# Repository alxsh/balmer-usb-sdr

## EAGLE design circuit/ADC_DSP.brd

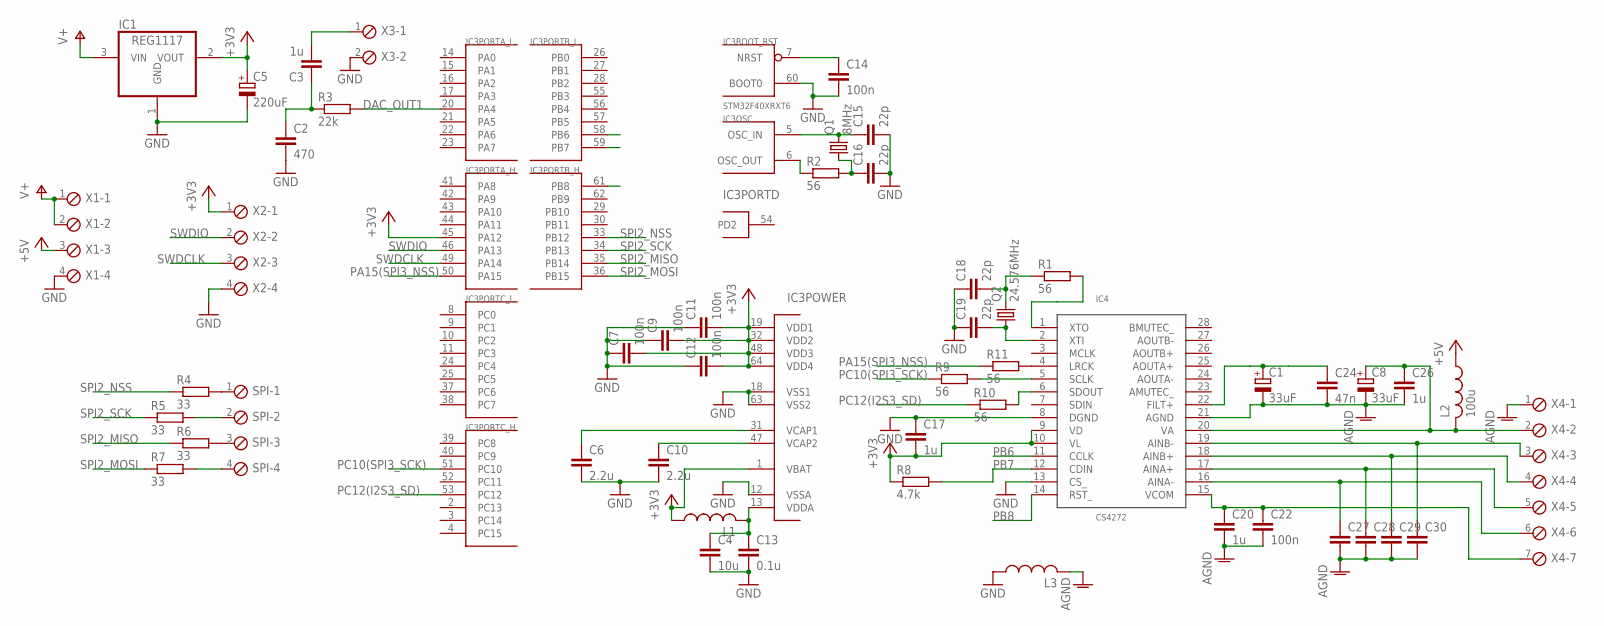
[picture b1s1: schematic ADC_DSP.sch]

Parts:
C1, C8: 33uF; 153CLV-0605
C2: 470; C0603
C3, C17, C20, C26: 1u; C0603
C4: 10u; C0805
C5: 220uF; 153CLV-0605
C6, C10: 2.2u; C0603
C7, C9, C11, C12, C14, C22: 100n; C0603
C13: 0.1u; C0603
C15, C16, C18, C19: 22p; C0603
C24: 47n; C0805
C27, C28, C29, C30: C-EUC0805; C0805
IC1: REG1117; SOT223
IC3: STM32F40XRXT6; TQFP64
IC4: CS4272; TSSOP28
L1, L3: L-USL2012C; L2012C
L2: 100u; 0207/12
Q1: 8MHz; HC49/S
Q2: 24.576MHz; HC49/S
R1, R2, R9, R10, R11: 56; R0603
R3: 22k; R0603
R4, R5, R6, R7: 33; R0603
R8: 4.7k; R0603
SPI: MPT4; 4POL254
X1, X2: MPT4; 4POL254
X3: MPT2; 2POL254
X4: MPT7; 7POL254

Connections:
+3V3: C5.+, C7.2, C9.2, C11.2, C12.2, C17.2, IC1.2 (VOUT), IC3.1 (VBAT), IC3.19 (VDD1), IC3.32 (VDD2), IC3.45 (PA12), IC3.48 (VDD3), IC3.64 (VDD4), IC4.9 (VD), IC4.10 (VL), L1.1, R8.1, X2.1
+5V: L2.1, X1.3
AGND: C1.-, C8.-, C20.2, C22.2, C24.2, C26.2, C27.2, C28.2, C29.2, C30.2, IC4.21 (AGND), L3.2, X4.1
AINA+: C28.1, IC4.17 (AINA+), X4.5
AINB+: C29.1, IC4.18 (AINB+), X4.4
AVCC: C8.+, C26.1, IC4.20 (VA), L2.2, X4.2
DAC_OUT1: IC3.20 (PA4), R3.2
GND: C2.2, C4.2, C5.-, C6.2, C7.1, C9.1, C10.2, C11.1, C12.1, C13.2, C14.2, C15.2, C16.2, C17.1, C18.1, C19.1, IC1.1 (GND), IC3.12 (VSSA), IC3.18 (VSS1), IC3.60 (BOOT0), IC3.63 (VSS2), IC4.8 (DGND), IC4.13 (CS_), L3.1, X1.4, X2.4, X3.2
unnamed: C10.1, IC3.47 (VCAP2)
unnamed: C6.1, IC3.31 (VCAP1)
unnamed: C4.1, C13.1, IC3.13 (VDDA), L1.2
unnamed: C14.1, IC3.7 (NRST)
unnamed: C15.1, IC3.5 (OSC_IN), Q1.2
unnamed: C16.1, Q1.1, R2.2
unnamed: C19.2, IC4.2 (XTI), Q2.1
unnamed: C18.2, Q2.2, R1.1
unnamed: IC4.4 (LRCK), R11.2
unnamed: IC4.5 (SCLK), R9.2
unnamed: IC4.6 (SDOUT), R10.2
unnamed: C1.+, C24.1, IC4.22 (FILT+)
unnamed: C30.1, IC4.19 (AINB-), X4.3
unnamed: C3.2, X3.1
unnamed: IC4.1 (XTO), R1.2
unnamed: C27.1, IC4.16 (AINA-), X4.6
unnamed: IC3.6 (OSC_OUT), R2.1
unnamed: R4.2, SPI.1
unnamed: R5.2, SPI.2
unnamed: R6.2, SPI.3
unnamed: C2.1, C3.1, R3.1
unnamed: R7.2, SPI.4
PA15(SPI3_NSS): IC3.50 (PA15), R11.1
PB6: IC3.58 (PB6), IC4.11 (CCLK)
PB7: IC3.59 (PB7), IC4.12 (CDIN), R8.2
PB8: IC3.61 (PB8), IC4.14 (RST_)
PC10(SPI3_SCK): IC3.51 (PC10), R9.1
PC12(I2S3_SD): IC3.53 (PC12), R10.1
SPI2_MISO: IC3.35 (PB14), R6.1
SPI2_MOSI: IC3.36 (PB15), R7.1
SPI2_NSS: IC3.33 (PB12), R4.1
SPI2_SCK: IC3.34 (PB13), R5.1
SWDCLK: IC3.49 (PA14), X2.3
SWDIO: IC3.46 (PA13), X2.2
V+: IC1.3 (VIN), X1.1, X1.2
VCOM: C20.1, C22.1, IC4.15 (VCOM), X4.7

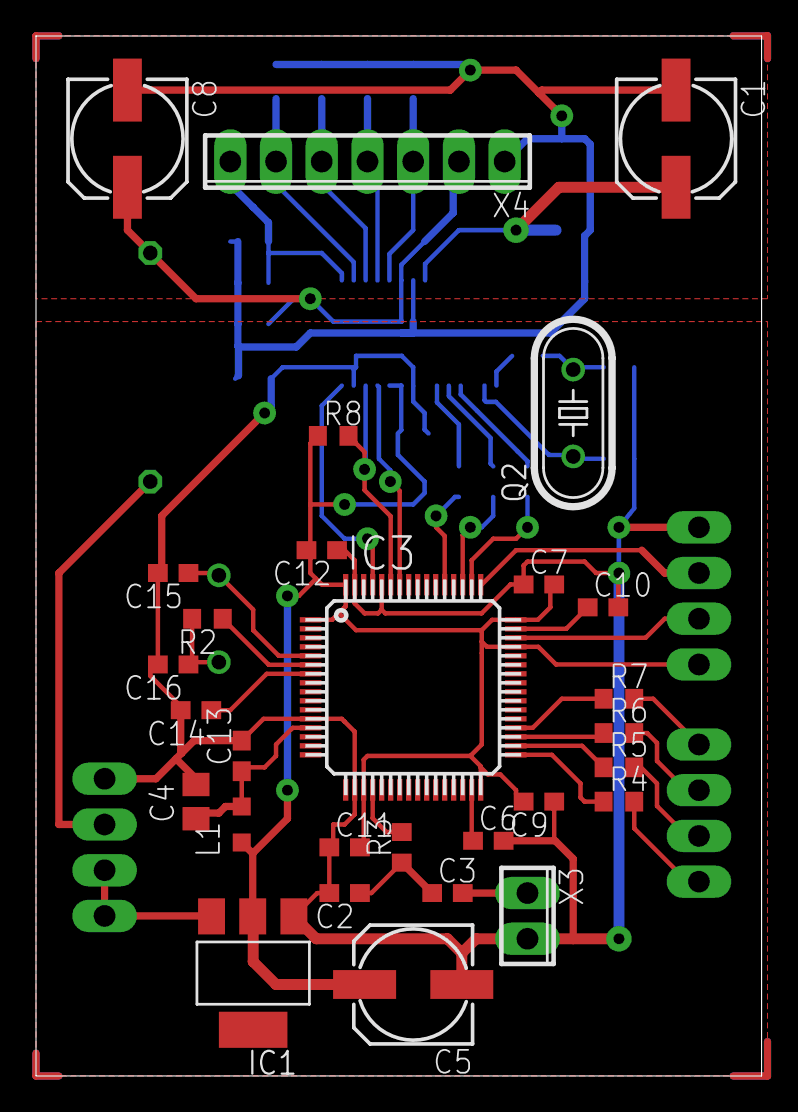
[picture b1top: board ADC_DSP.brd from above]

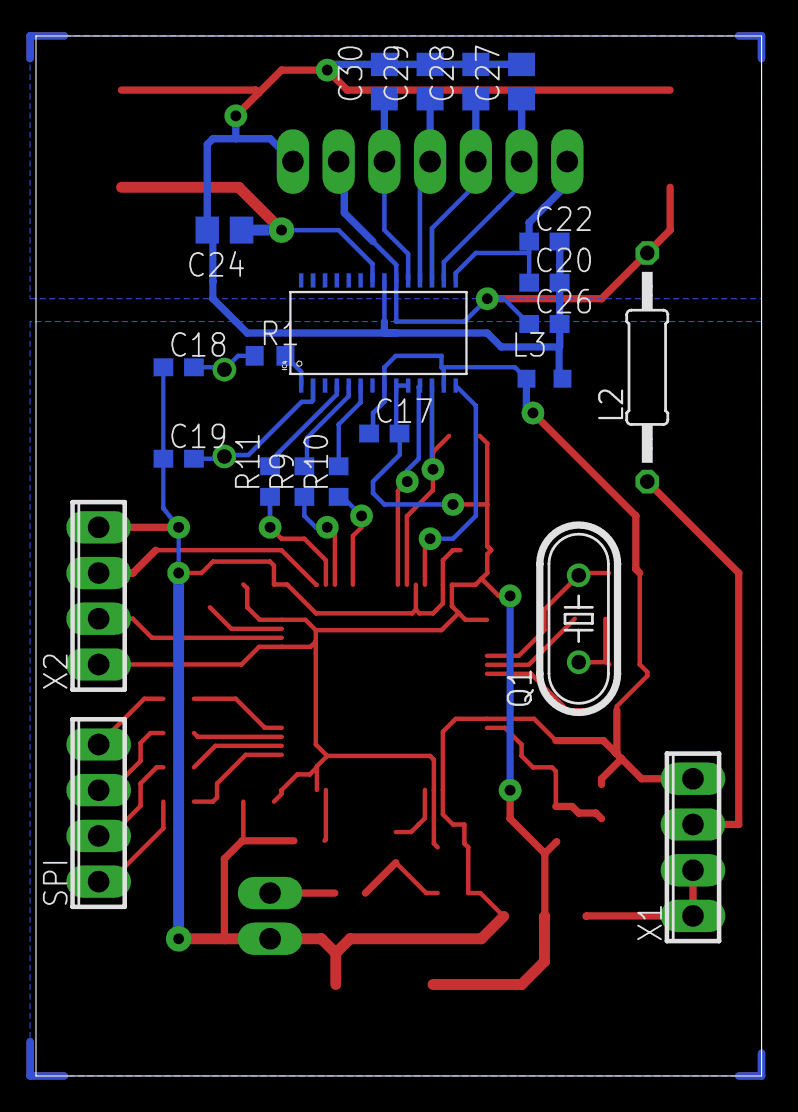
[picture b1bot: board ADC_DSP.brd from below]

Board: 2 copper layers, 40.3 x 57.8 mm, 51 parts (22 on the bottom side), 44 nets.

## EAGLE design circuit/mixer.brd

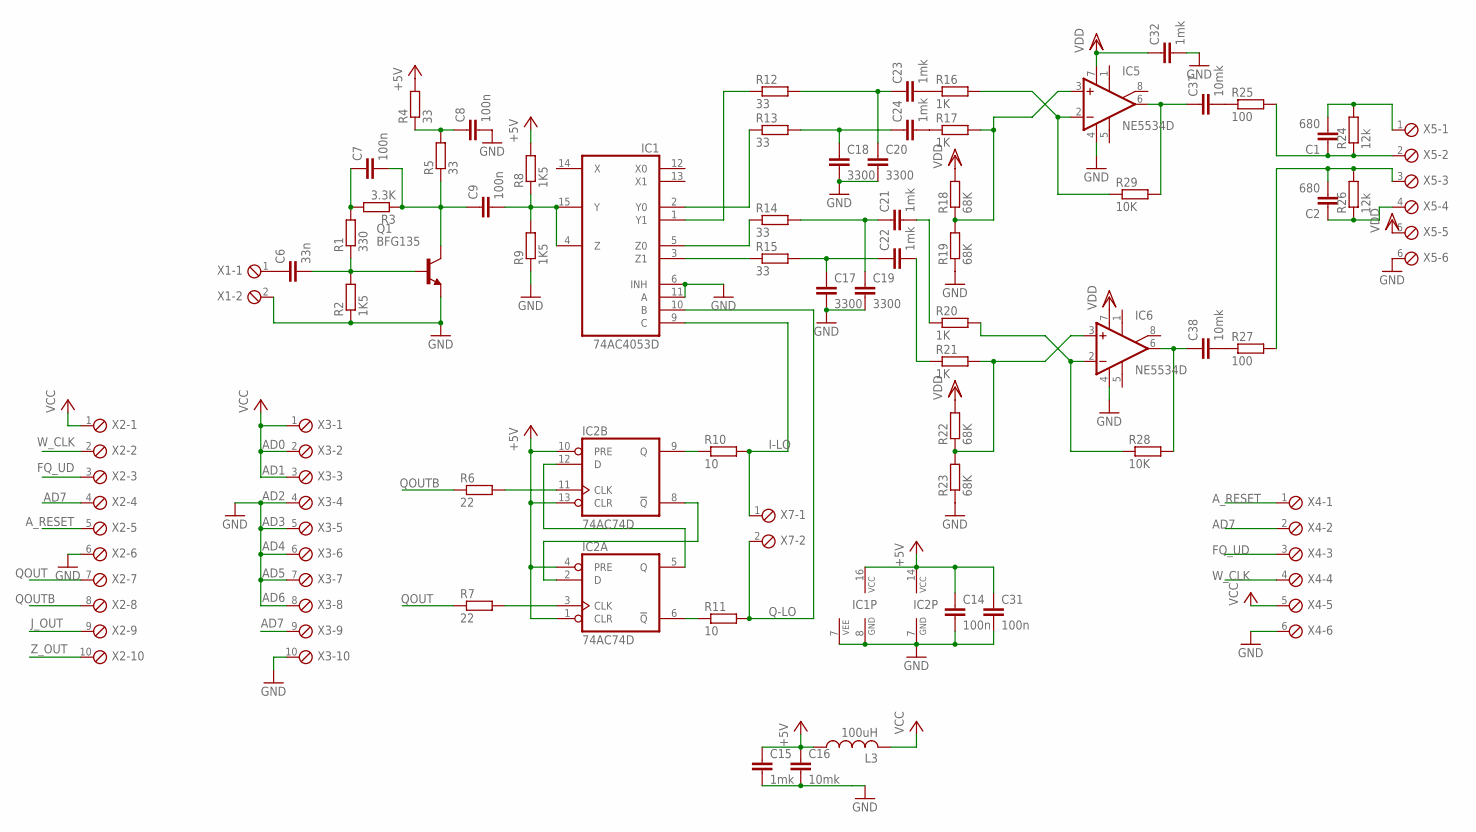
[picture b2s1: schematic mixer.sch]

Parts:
C1, C2: 680; C0805
C6: 33n; C0805
C7, C8, C9, C14, C31: 100n; C0603
C15, C21, C22, C23, C24, C32: 1mk; C0603
C16, C37, C38: 10mk; C0805
C17, C18, C19, C20: 3300; C0805
IC1: 74AC4053D; SO16
IC2: 74AC74D; SO14
IC5, IC6: NE5534D; SO08
L3: 100uH; 0207/12
Q1: BFG135; SOT223
R1: 330; R0603
R2, R8, R9: 1K5; R0603
R3: 3.3K; R0603
R4, R5, R12, R13, R14, R15: 33; R0603
R6, R7: 22; R0603
R10, R11: 10; R0603
R16, R17, R20, R21: 1K; R0603
R18, R19, R22, R23: 68K; R0603
R24, R26: 12k; R0603
R25, R27: 100; R0603
R28, R29: 10K; R0603
X1, X7: MPT2; 2POL254
X2, X3: MPT10; 10POL254
X4, X5: MPT6; 6POL254

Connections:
+5V: C14.1, C15.1, C16.1, C31.1, IC1.16 (VCC), IC2.1 (CLR), IC2.4 (PRE), IC2.10 (PRE), IC2.13 (CLR), IC2.14 (VCC), L3.1, R4.2, R8.2
AD7: X2.4, X4.2
A_RESET: X2.5, X4.1
FQ_UD: X2.3, X4.3
GND: C8.2, C14.2, C15.2, C16.2, C17.2, C18.2, C19.2, C20.2, C31.2, C32.2, IC1.6 (INH), IC1.7 (VEE), IC1.8 (GND), IC1.11 (A), IC2.7 (GND), IC5.4 (V-), IC6.4 (V-), Q1.1 (E), Q1.3 (E), R2.1, R9.1, R19.1, R23.1, X1.2, X2.6, X3.4, X3.5, X3.6, X3.7, X3.8, X3.10, X4.6, X5.6
I-LO: IC1.9 (C), R10.2, X7.1
J_OUT: X2.9
unnamed: IC2.5 (Q), IC2.12 (D)
unnamed: IC2.2 (D), IC2.8 (!Q)
unnamed: IC2.11 (CLK), R6.2
unnamed: IC2.3 (CLK), R7.2
unnamed: IC1.3 (Z1), R15.1
unnamed: C9.2, IC1.4 (Z), IC1.15 (Y), R8.1, R9.2
unnamed: C7.1, R1.2, R3.2
unnamed: IC1.5 (Z0), R14.1
unnamed: IC1.2 (Y0), R13.1
unnamed: IC1.1 (Y1), R12.1
unnamed: C17.1, C22.1, R15.2
unnamed: C19.1, C21.1, R14.2
unnamed: C18.1, C24.1, R13.2
unnamed: C20.1, C23.1, R12.2
unnamed: IC5.3 (+IN), R17.2, R18.1, R19.2
unnamed: C38.1, IC6.6 (OUT), R28.2
unnamed: IC5.2 (-IN), R16.2, R29.1
unnamed: C37.1, IC5.6 (OUT), R29.2
unnamed: C23.2, R16.1
unnamed: C21.2, R20.1
unnamed: C22.2, R21.1
unnamed: IC6.2 (-IN), R20.2, R28.1
unnamed: IC6.3 (+IN), R21.2, R22.1, R23.2
unnamed: C6.1, X1.1
unnamed: C24.2, R17.1
unnamed: C37.2, R25.1
unnamed: C1.1, R24.1, R25.2, X5.2
unnamed: C1.2, R24.2, X5.1
unnamed: C2.1, R26.1, X5.4
unnamed: C2.2, R26.2, R27.2, X5.3
unnamed: IC2.9 (Q), R10.1
unnamed: IC2.6 (!Q), R11.1
unnamed: C38.2, R27.1
unnamed: C7.2, C9.1, Q1.4 (C), R3.1, R5.1
unnamed: C8.1, R4.1, R5.2
unnamed: C6.2, Q1.2 (B), R1.1, R2.2
Q-LO: IC1.10 (B), R11.2, X7.2
QOUT: R7.1, X2.7
QOUTB: R6.1, X2.8
VCC: L3.2, X2.1, X3.1, X3.2, X3.3, X4.5
VDD: C32.1, IC5.7 (V+), IC6.7 (V+), R18.2, R22.2, X5.5
W_CLK: X2.2, X4.4
Z_OUT: X2.10

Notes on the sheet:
AD0
AD1
AD2
AD3
AD4
AD5
AD6
AD7

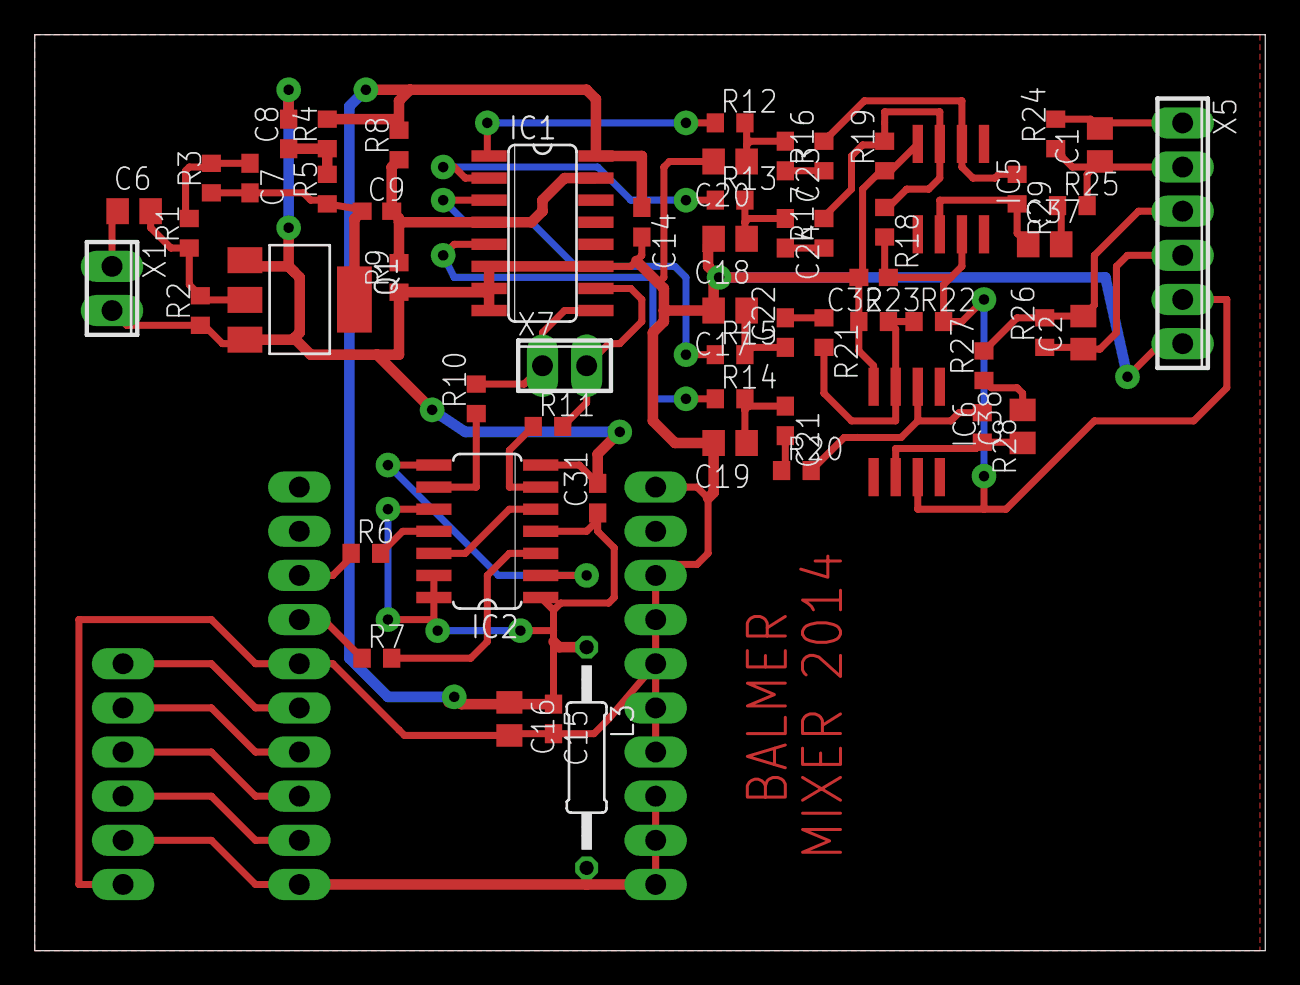
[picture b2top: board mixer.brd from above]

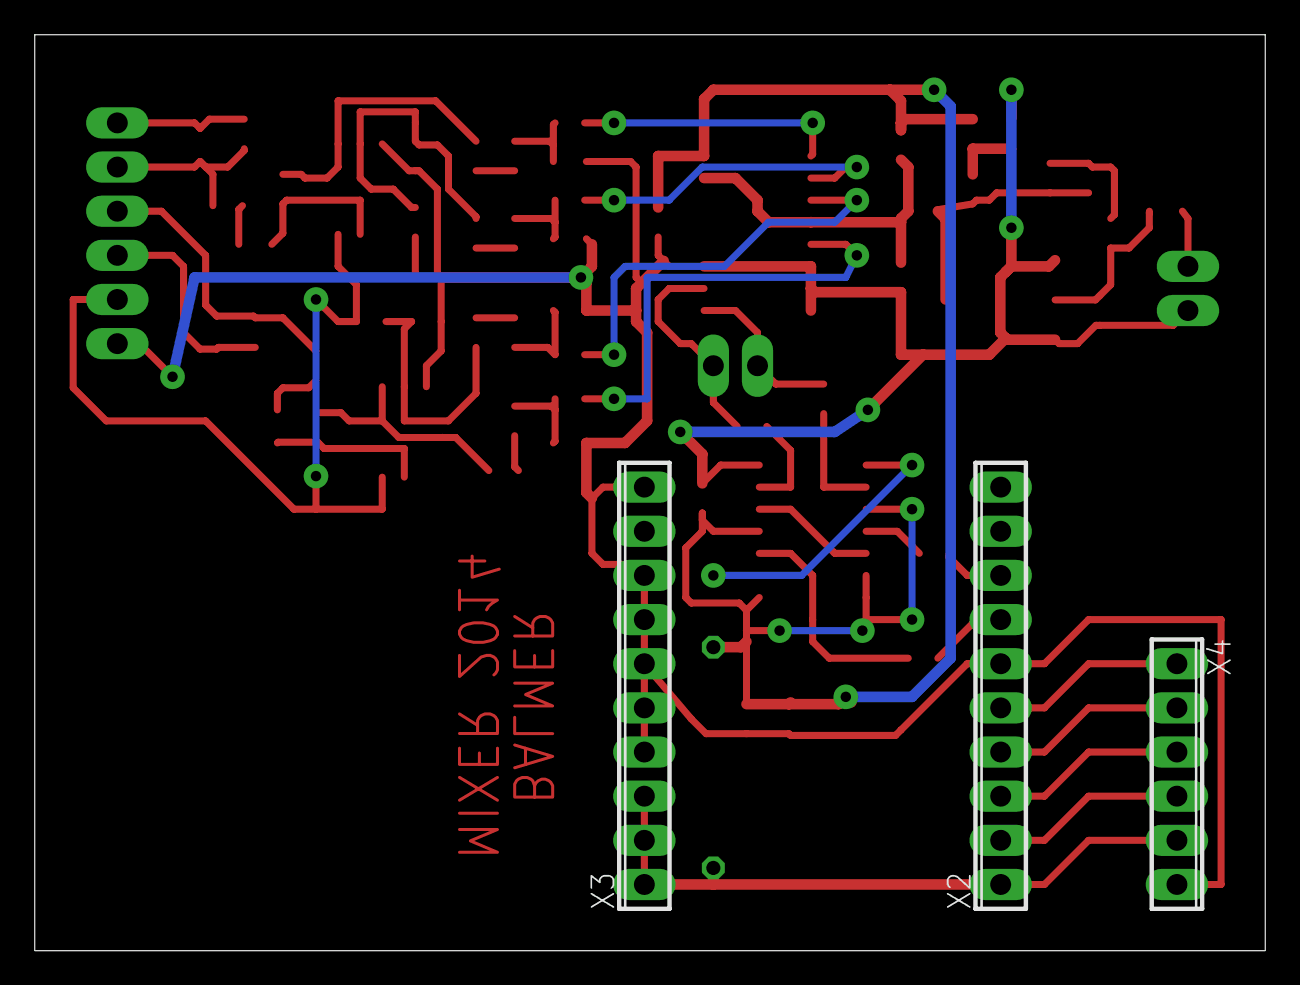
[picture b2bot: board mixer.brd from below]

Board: 2 copper layers, 70.8 x 52.7 mm, 62 parts (3 on the bottom side), 48 nets.

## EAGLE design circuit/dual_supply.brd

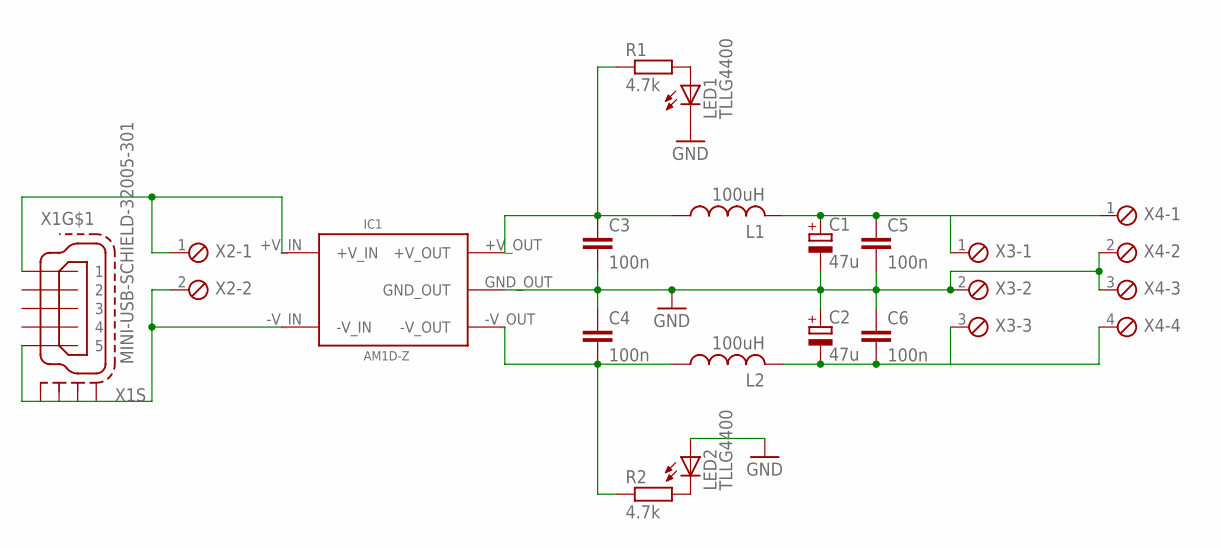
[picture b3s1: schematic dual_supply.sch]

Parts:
C1, C2: 47u; E3,5-8
C3, C4, C5, C6: 100n; C0805
IC1: AM1D-Z
L1, L2: 100uH; IR-2
LED1, LED2: TLLG4400; LED3MM
R1, R2: 4.7k; R0805
X1: MINI-USB-SCHIELD-32005-301; 32005-301
X2: MPT2; 2POL254
X3: MPT3; 3POL254
X4: MPT4; 4POL254

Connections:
+5V: C1.+, C5.1, L1.2, X3.1, X4.1
-5V: C2.-, C6.2, L2.2, X3.3, X4.4
GND: C1.-, C2.+, C3.2, C4.1, C5.2, C6.1, IC1.GND_OUT, LED1.K (C), LED2.A, X3.2, X4.2, X4.3
unnamed: IC1.-V_IN, X1.5, X1.M1 (S1), X1.M2 (S2), X1.M3 (S3), X1.M4 (S4), X2.2
unnamed: IC1.+V_IN, X1.1, X2.1
unnamed: C3.1, IC1.+V_OUT, L1.1, R1.1
unnamed: LED1.A, R1.2
unnamed: C4.2, IC1.-V_OUT, L2.1, R2.1
unnamed: LED2.K (C), R2.2

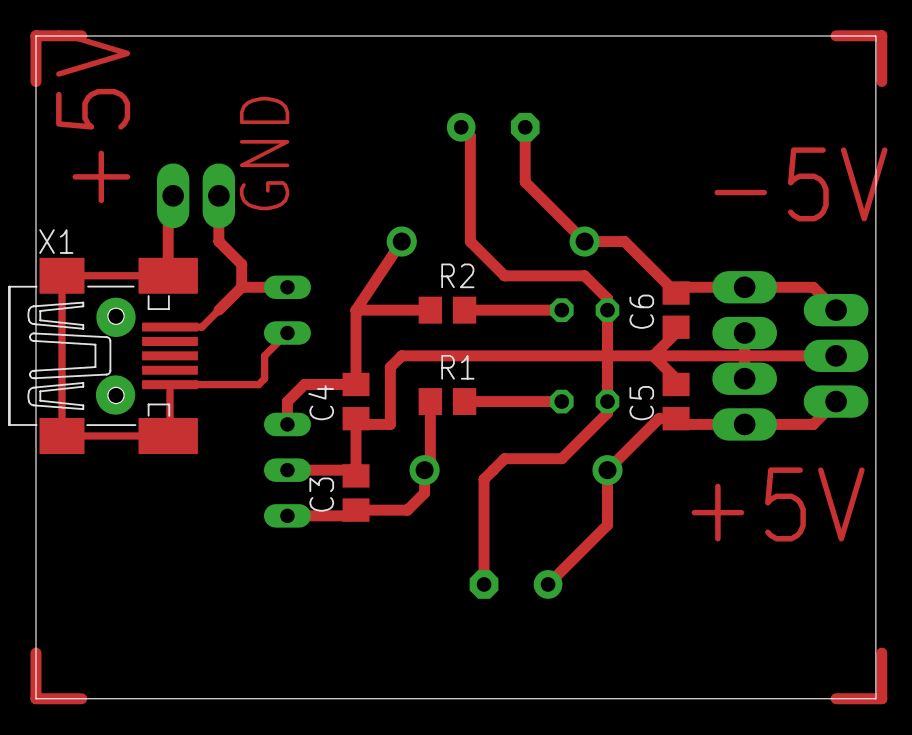
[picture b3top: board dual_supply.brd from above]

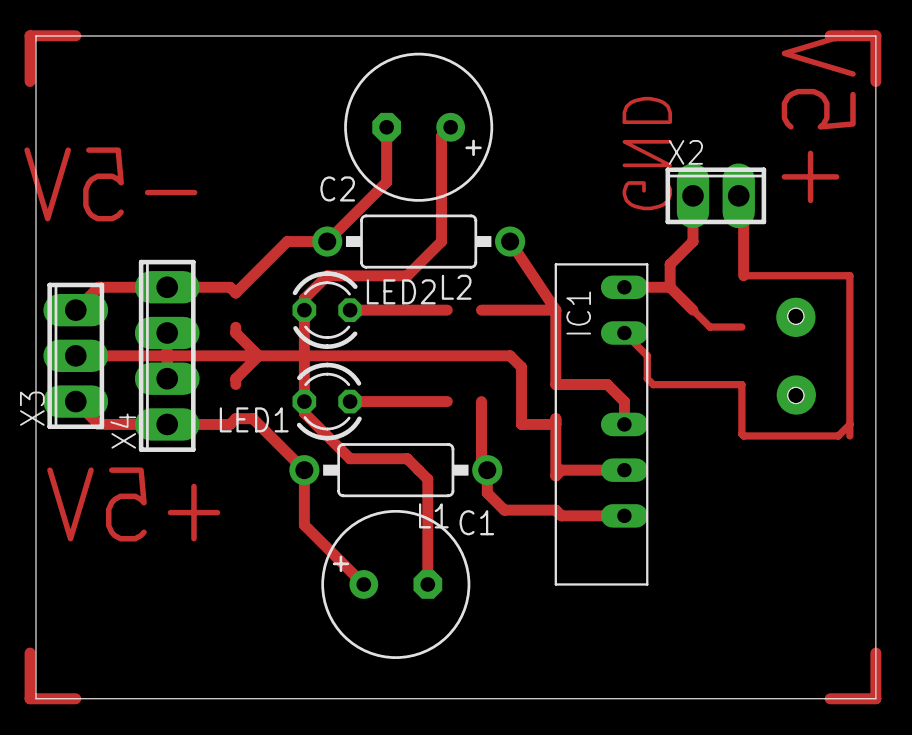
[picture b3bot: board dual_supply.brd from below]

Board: 2 copper layers, 46.7 x 36.8 mm, 17 parts (10 on the bottom side), 9 nets.

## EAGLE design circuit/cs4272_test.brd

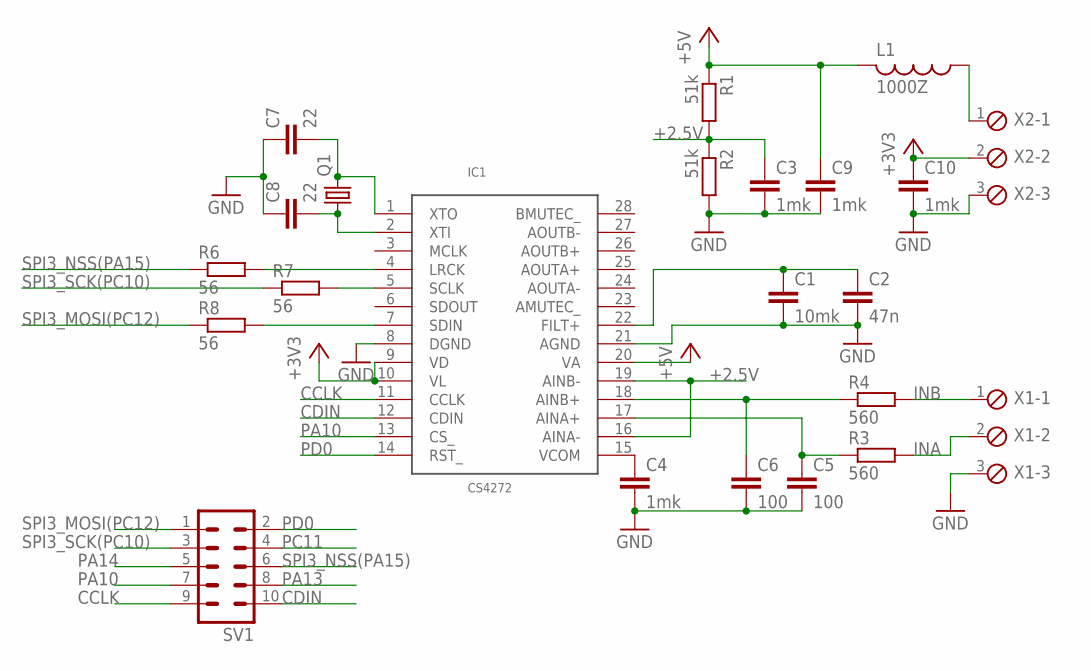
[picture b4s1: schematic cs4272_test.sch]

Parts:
C1: 10mk; C0805
C2: 47n; C0805
C3, C4, C9, C10: 1mk; C0603
C5, C6: 100; C0805
C7, C8: 22; C0603
IC1: CS4272; TSSOP28
L1: 1000Z; C0805
Q1: CRYSTALHC49S; HC49/S
R1, R2: 51k; R0603
R3, R4: 560; R0603
R6, R7, R8: 56; R0603
SV1: ML10
X1, X2: MPT3; 3POL254

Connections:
+2.5V: C3.1, IC1.16 (AINA-), IC1.19 (AINB-), R1.2, R2.1
+3V3: C10.1, IC1.9 (VD), IC1.10 (VL), X2.2
+5V: C9.1, IC1.20 (VA), L1.2, R1.1
CCLK: IC1.11 (CCLK), SV1.9
CDIN: IC1.12 (CDIN), SV1.10
GND: C1.2, C2.2, C3.2, C4.2, C5.2, C6.2, C7.1, C8.1, C9.2, C10.2, IC1.8 (DGND), IC1.21 (AGND), R2.2, X1.3, X2.3
INA: R3.2, X1.2
INB: R4.2, X1.1
unnamed: C1.1, C2.1, IC1.22 (FILT+)
unnamed: C4.1, IC1.15 (VCOM)
unnamed: C6.1, IC1.18 (AINB+), R4.1
unnamed: C5.1, IC1.17 (AINA+), R3.1
unnamed: C8.2, IC1.2 (XTI), Q1.1
unnamed: C7.2, IC1.1 (XTO), Q1.2
unnamed: L1.1, X2.1
unnamed: IC1.4 (LRCK), R6.2
unnamed: IC1.5 (SCLK), R7.2
unnamed: IC1.7 (SDIN), R8.2
PA10: IC1.13 (CS_), SV1.7
PA13: SV1.8
PA14: SV1.5
PC11: SV1.4
PD0: IC1.14 (RST_), SV1.2
SPI3_MOSI(PC12): R8.1, SV1.1
SPI3_NSS(PA15): R6.1, SV1.6
SPI3_SCK(PC10): R7.1, SV1.3

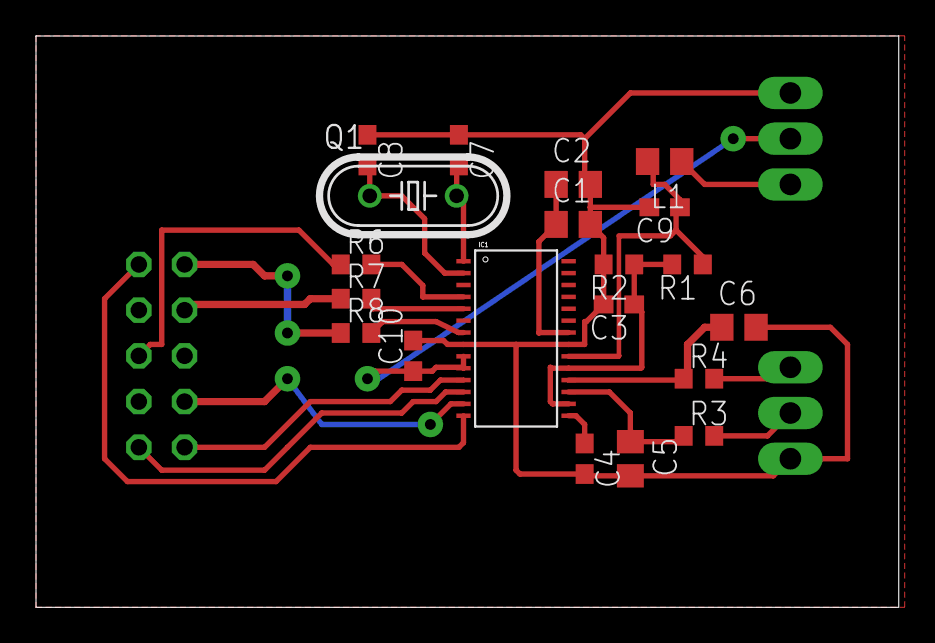
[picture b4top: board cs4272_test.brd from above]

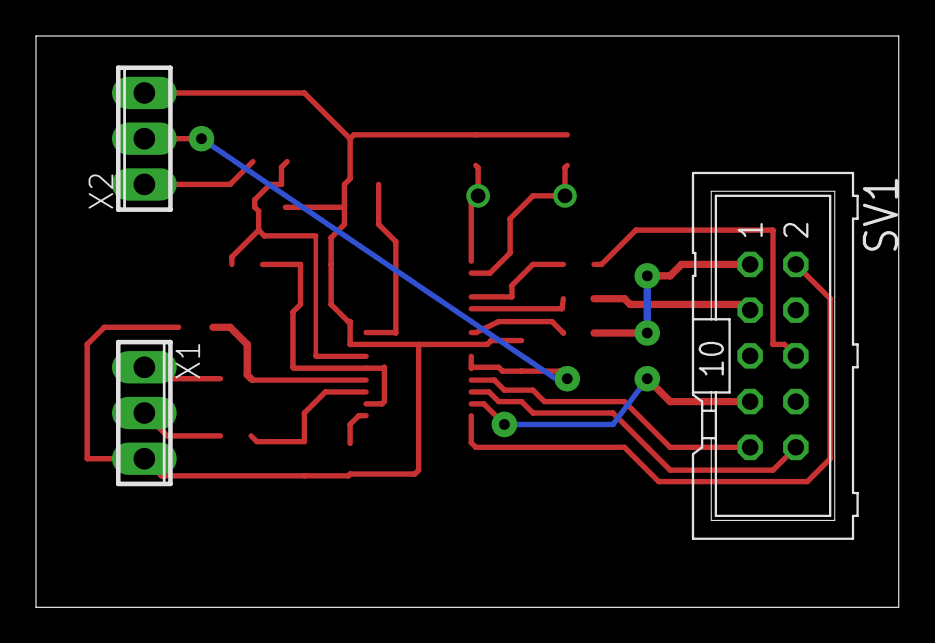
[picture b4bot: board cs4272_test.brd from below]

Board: 2 copper layers, 47.9 x 31.7 mm, 23 parts (3 on the bottom side), 23 nets.

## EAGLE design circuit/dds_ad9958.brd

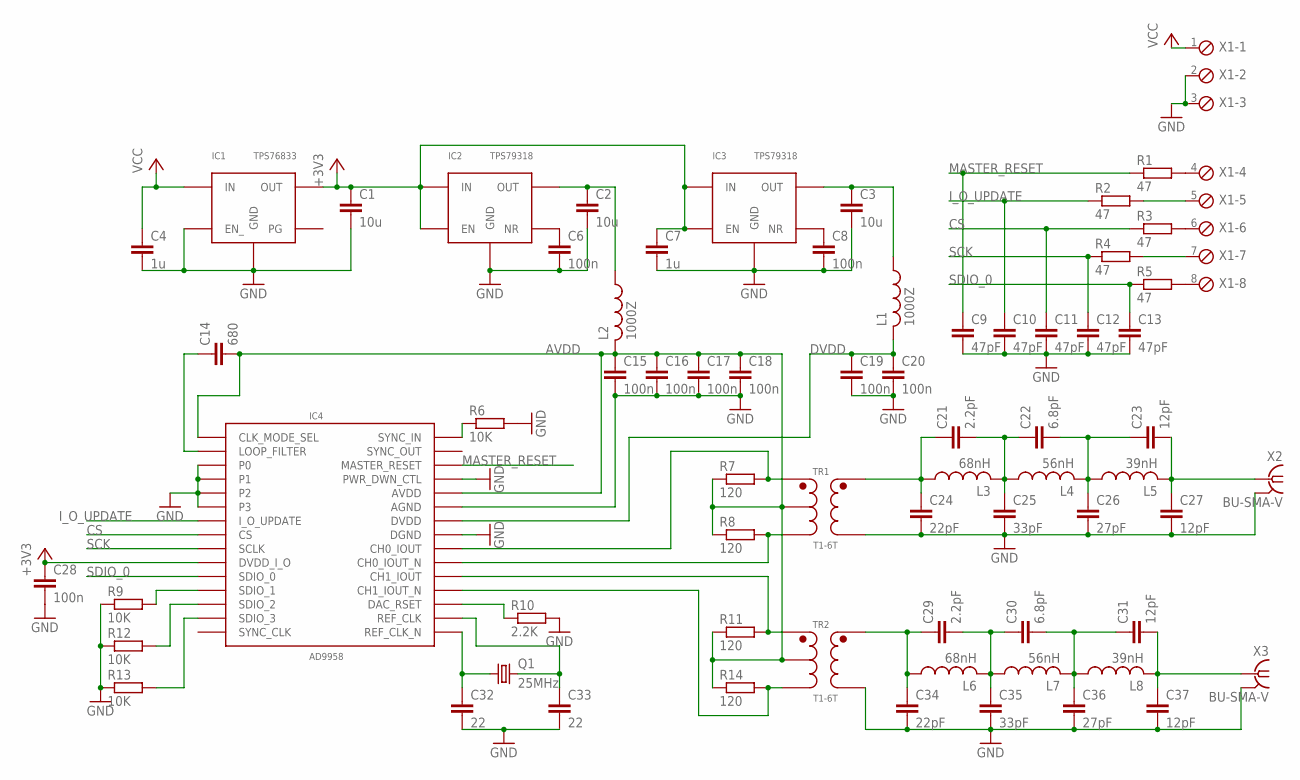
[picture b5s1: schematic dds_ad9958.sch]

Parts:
C1, C2, C3: 10u; C0805
C4, C7: 1u; C0603
C6, C8, C15, C16, C17, C18, C19, C20, C28: 100n; C0603
C9, C10, C11, C12, C13: 47pF; C0805
C14: 680; C0805
C21, C29: 2.2pF; C0805
C22, C30: 6.8pF; C0805
C23, C27, C31, C37: 12pF; C0805
C24, C34: 22pF; C0805
C25, C35: 33pF; C0805
C26, C36: 27pF; C0805
C32, C33: 22; C0603
IC1: TPS76833; SO8
IC2, IC3: TPS79318; SOT23-5
IC4: AD9958; CP-56-1
L1, L2: 1000Z; C0805
L3, L6: 68nH; C0805
L4, L7: 56nH; C0805
L5, L8: 39nH; C0805
Q1: 25MHz; HC49/S
R1, R2, R3, R4, R5: 47; R0603
R6, R9, R12, R13: 10K; R0603
R7, R8, R11, R14: 120; R0603
R10: 2.2K; R0603
TR1, TR2: T1-6T; KK81
X1: MPT8; 8POL254
X2, X3: BU-SMA-V

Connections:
+3V3: C1.1, C7.1, C28.1, IC1.5 (OUT), IC1.6 (OUT), IC2.1 (IN), IC2.3 (EN), IC3.1 (IN), IC3.3 (EN), IC4.P$49 (DVDD_I_O)
AVDD: C14.2, C15.1, C16.1, C17.1, C18.1, IC4.P$5 (AVDD), IC4.P$7 (AVDD), IC4.P$11 (AVDD), IC4.P$15 (AVDD), IC4.P$19 (AVDD), IC4.P$21 (AVDD), IC4.P$24 (CLK_MODE_SEL), IC4.P$26 (AVDD), IC4.P$29 (AVDD), IC4.P$30 (AVDD), IC4.P$31 (AVDD), IC4.P$33 (AVDD), IC4.P$35 (AVDD), IC4.P$36 (AVDD), IC4.P$37 (AVDD), IC4.P$39 (AVDD), L2.2, R7.1, R8.1, R11.1, R14.1, TR1.P$2 (SEC_CT), TR2.P$2 (SEC_CT)
CS: C11.1, IC4.P$47 (CS), R3.1
DVDD: C19.1, C20.1, IC4.P$45 (DVDD), IC4.P$55 (DVDD), L1.2
GND: C1.2, C2.2, C3.2, C4.2, C6.2, C7.2, C8.2, C9.2, C10.2, C11.2, C12.2, C13.2, C15.2, C16.2, C17.2, C18.2, C19.2, C20.2, C24.2, C25.2, C26.2, C27.2, C28.2, C32.2, C33.2, C34.2, C35.2, C36.2, C37.2, IC1.1 (GND), IC1.2 (EN_), IC2.2 (GND), IC3.2 (GND), IC4.P$4 (PWR_DWN_CTL), IC4.P$6 (AGND), IC4.P$10 (AGND), IC4.P$12 (AGND), IC4.P$16 (AGND), IC4.P$18 (AGND), IC4.P$20 (AGND), IC4.P$25 (AGND), IC4.P$40 (P0), IC4.P$41 (P1), IC4.P$42 (P2), IC4.P$43 (P3), IC4.P$44 (DGND), IC4.P$56 (DGND), IC4.PAD (AGND), R6.2, R9.1, R10.2, R12.1, R13.1, TR1.P$6 (PRI), TR2.P$6 (PRI), X1.2, X1.3, X2.2, X2.3 (2), X2.4 (2), X2.5 (2), X3.2, X3.3 (2), X3.4 (2), X3.5 (2)
I_O_UPDATE: C10.1, IC4.P$46 (I_O_UPDATE), R2.1
MASTER_RESET: C9.1, IC4.P$3 (MASTER_RESET), R1.1
unnamed: C32.1, IC4.P$22 (REF_CLK_N), Q1.1
unnamed: C21.1, C24.1, L3.1, TR1.P$4 (PRI_DOT)
unnamed: IC4.P$8 (CH0_IOUT), R7.2, TR1.P$3 (SEC_DOT)
unnamed: C6.1, IC2.4 (NR)
unnamed: C8.1, IC3.4 (NR)
unnamed: C2.1, IC2.5 (OUT), L2.1
unnamed: IC4.P$9 (CH0_IOUT_N), R8.2, TR1.P$1 (SEC)
unnamed: C3.1, IC3.5 (OUT), L1.1
unnamed: IC4.P$13 (CH1_IOUT), R11.2, TR2.P$3 (SEC_DOT)
unnamed: IC4.P$14 (CH1_IOUT_N), R14.2, TR2.P$1 (SEC)
unnamed: C21.2, C22.1, C25.1, L3.2, L4.1
unnamed: IC4.P$17 (DAC_RSET), R10.1
unnamed: IC4.P$51 (SDIO_1), R9.2
unnamed: IC4.P$1 (SYNC_IN), R6.1
unnamed: C14.1, IC4.P$27 (LOOP_FILTER)
unnamed: C33.1, IC4.P$23 (REF_CLK), Q1.2
unnamed: C22.2, C23.1, C26.1, L4.2, L5.1
unnamed: C23.2, C27.1, L5.2, X2.1
unnamed: IC4.P$52 (SDIO_2), R12.2
unnamed: IC4.P$53 (SDIO_3), R13.2
unnamed: C29.1, C34.1, L6.1, TR2.P$4 (PRI_DOT)
unnamed: C29.2, C30.1, C35.1, L6.2, L7.1
unnamed: C30.2, C31.1, C36.1, L7.2, L8.1
unnamed: C31.2, C37.1, L8.2, X3.1
unnamed: R3.2, X1.6
unnamed: R5.2, X1.8
unnamed: R1.2, X1.4
unnamed: R2.2, X1.5
unnamed: R4.2, X1.7
SCK: C12.1, IC4.P$48 (SCLK), R4.1
SDIO_0: C13.1, IC4.P$50 (SDIO_0), R5.1
VCC: C4.1, IC1.3 (IN), IC1.4 (IN), X1.1

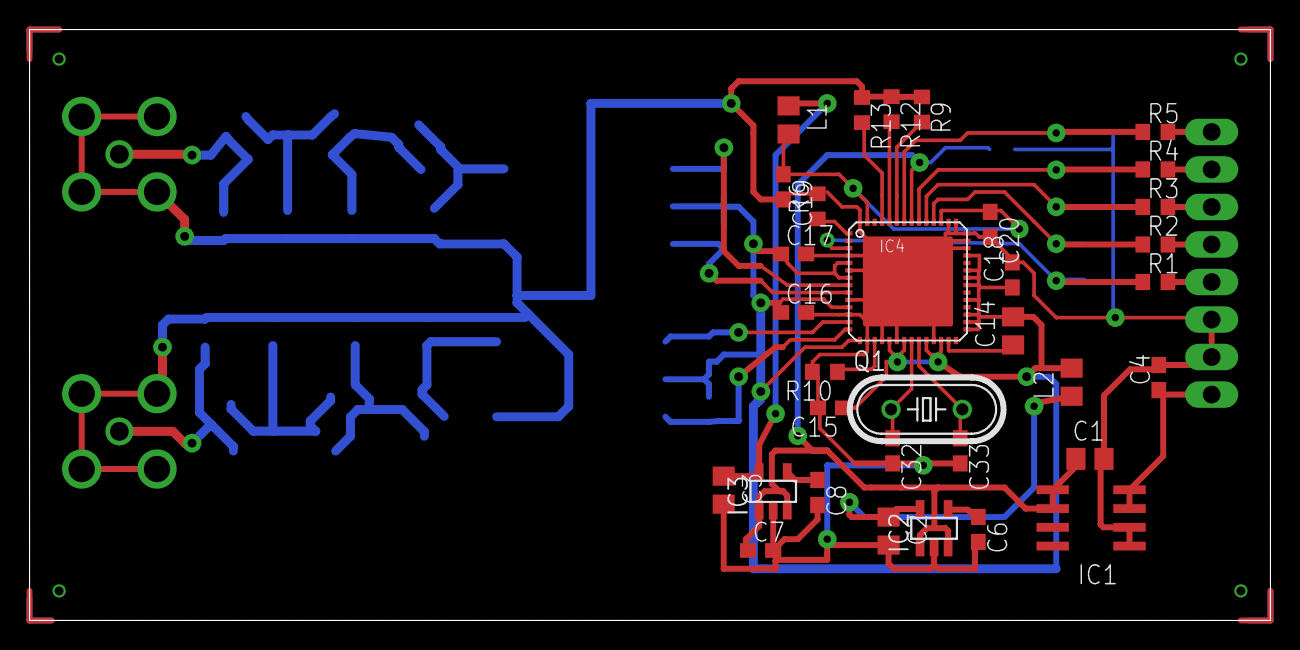
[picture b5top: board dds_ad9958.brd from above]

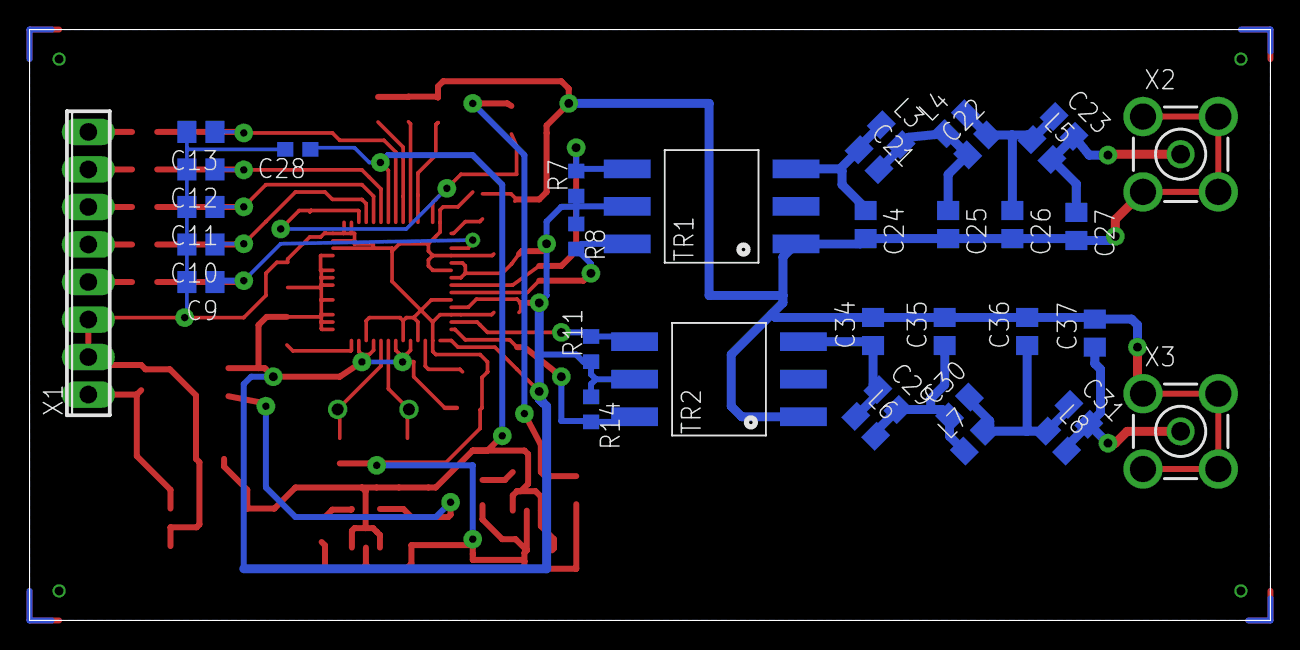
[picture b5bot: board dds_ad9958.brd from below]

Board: 2 copper layers, 84.0 x 40.0 mm, 68 parts (35 on the bottom side), 39 nets.

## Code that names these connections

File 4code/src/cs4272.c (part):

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#include "delay.h"
#include "process_sound.h"

//	CCLK - PB6
//	CDIN - PB7
//  RST - PB8

// SPI3_NSS PA15
// SPI3_SCK PC10
// I2S3_SD  PC12



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	/* setup SCL and SDA pins
	 * You can connect I2C1 to two different
	 * pairs of pins:
	 * 1. SCL on PB6 and SDA on PB7
	 * 2. SCL on PB8 and SDA on PB9
	 */
	GPIO_InitStruct.GPIO_Pin = GPIO_Pin_6 | GPIO_Pin_7; // we are going to use PB6 and PB7
	GPIO_InitStruct.GPIO_Mode = GPIO_Mode_AF;			// set pins to alternate function
	GPIO_InitStruct.GPIO_Speed = GPIO_Speed_2MHz;//GPIO_Speed_50MHz;		// set GPIO speed
	GPIO_InitStruct.GPIO_OType = GPIO_OType_OD;			// set output to open drain --> the line has to be only pulled low, not driven high
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	I2S_InitTypeDef I2S_InitStruct;

	//I2S3 used
	//PA15 - NSS
	//PC10 - SCK
	//PC12 - MOSI
	RCC_APB1PeriphClockCmd(RCC_APB1Periph_SPI3, ENABLE);
	RCC_AHB1PeriphClockCmd(RCC_AHB1Periph_DMA1, ENABLE);
	RCC_AHB1PeriphClockCmd(RCC_AHB1Periph_GPIOA|RCC_AHB1Periph_GPIOC, ENABLE);
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
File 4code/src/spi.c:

#include "delay.h"
#include "spi.h"
#include "spi_data_process.h"
/*
	EXTI Slave 			 - PB12
	SPI2_SCK             - PB13 34 *
	SPI2_MISO            - PB14 35 *
	SPI2_MOSI            - PB15 36 *
*/

void SpiInit()
{
	GPIO_InitTypeDef GPIO_InitStructure;
	SPI_InitTypeDef SPI_InitStructure;
	RCC_APB1PeriphClockCmd(RCC_APB1Periph_SPI2, ENABLE);
	RCC_AHB1PeriphClockCmd(RCC_AHB1Periph_GPIOB, ENABLE);

	GPIO_InitStructure.GPIO_Pin = GPIO_Pin_13 | GPIO_Pin_14 | GPIO_Pin_15;
	GPIO_InitStructure.GPIO_Mode = GPIO_Mode_AF;
	GPIO_InitStructure.GPIO_Speed = GPIO_Speed_25MHz;
	GPIO_InitStructure.GPIO_OType = GPIO_OType_PP;
	GPIO_InitStructure.GPIO_PuPd = GPIO_PuPd_NOPULL;
	GPIO_Init(GPIOB, &GPIO_InitStructure);

	GPIO_InitStructure.GPIO_Pin = GPIO_Pin_12;
	GPIO_InitStructure.GPIO_Mode = GPIO_Mode_OUT;
	GPIO_InitStructure.GPIO_Speed = GPIO_Speed_25MHz;
	GPIO_InitStructure.GPIO_OType = GPIO_OType_PP;
	GPIO_InitStructure.GPIO_PuPd = GPIO_PuPd_NOPULL;
	GPIO_Init(GPIOB, &GPIO_InitStructure);

	GPIO_PinAFConfig(GPIOB, GPIO_PinSource13, GPIO_AF_SPI2);
	GPIO_PinAFConfig(GPIOB, GPIO_PinSource14, GPIO_AF_SPI2);
	GPIO_PinAFConfig(GPIOB, GPIO_PinSource15, GPIO_AF_SPI2);
	 
	SPI_InitStructure.SPI_Direction = SPI_Direction_2Lines_FullDuplex;
	SPI_InitStructure.SPI_DataSize = SPI_DataSize_16b;
	SPI_InitStructure.SPI_CPOL = SPI_CPOL_Low;
	SPI_InitStructure.SPI_CPHA = SPI_CPHA_1Edge;
	SPI_InitStructure.SPI_NSS = SPI_NSS_Soft;
	SPI_InitStructure.SPI_BaudRatePrescaler = SPI_BaudRatePrescaler_4;
	SPI_InitStructure.SPI_FirstBit = SPI_FirstBit_MSB;
	SPI_InitStructure.SPI_Mode = SPI_Mode_Slave;
	SPI_InitStructure.SPI_CRCPolynomial = 15;
	SPI_Init(SPI2, &SPI_InitStructure);

	SPI_I2S_ITConfig(SPI2, SPI_I2S_IT_RXNE,ENABLE);
	SPI_Cmd(SPI2, ENABLE);
	NVIC_EnableIRQ(SPI2_IRQn);

	SPI2->DR = 0x4003;
}

void SpiSend(uint16_t data)
{
	while( SPI2->SR & SPI_I2S_FLAG_BSY );
	SPI2->DR = data;
}

void SpiOnReceive()
{
	if (SPI_I2S_GetFlagStatus(SPI2, SPI_I2S_FLAG_RXNE)==SET) {
		volatile uint16_t data = SPI2->DR; //Читаем то что пришло
		SpiDataReceive(data);
	}
}

void SpiStartSend()
{
	GPIO_SetBits(GPIOB, GPIO_Pin_12);
}

void SpiEndSend()
{
	GPIO_ResetBits(GPIOB, GPIO_Pin_12);
}

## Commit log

2014-07-03 - first commit - uncomplete schematic
2014-07-03 - enable serial mode
2014-07-04 - change connector
2014-07-05 - ????????? ??????????? AD9850 ??????
2014-07-08 - ?????????????????? ?? ??????? 85x60??
2014-07-09 - ???????? ????? ??????? ? ????????? ???????? 78x61 ??
2014-07-09 - ????? ??? USB ?????
2014-07-15 - ?????????? USB ? ????????? ??????? ??? AD9850
2014-07-16 - ?????????? ? SdrDx ?????????
2014-07-21 - ????????? ????? - ?????????? ?????????? ?????? ??? IC5
2014-09-06 - ?????????? SDR audio ??? ????, ????? ????? ??????? ?????????? ?
2014-09-08 - AD8302 - AD9958
2014-09-08 - T1-6T, ???????? ? ???????????? Pinout
2014-09-09 - TPS76833 - TPS79318
2014-09-09 - ?????-???? ???????????? ????? ??? AD9958
2014-09-09 - renumber
2014-09-09 - ??????? SDR
2014-09-10 - ???????? ??????? AD9958
2014-09-28 - CS4272 test board
2014-10-15 - balmer.lbr CS4272 - STM32F405RGT6
2014-10-25 - ?????? ???????? DSP ??????
2014-10-26 - ??????? 51x57 ??
2014-10-26 - 43x55 ??
2014-10-28 - ????? ? ?????????? GND ? AGND
2014-11-02 - ????? ?????????? ?????? - ?????????? DelayUs, DelayMs. ????????? ?????? ? DelayUs ??-?? ??????? ?? ?????? ?? ??? ?????? (?????????? ? uint16_t) - ??? DAC ?????? ???????????? ???????, ?? ??? ???? ??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
2014-11-03 - R3 3.3 KOm -> 33 KOm C2 10 nF -> 1 nF - ???????? ??? ??? ?? ????????? DAC
2014-11-03 - ??????? ????????????? 48 ???
2014-11-03 - ????????? ??? ??????? ? SDR ???????????
2014-11-03 - SPI master 125 KHz
2014-11-03 - spi ??? STM32F405 (???? Master)
2014-11-04 - ?????????? ????? SPI - ??-?? ??????? ??????? ???????? ??? ?????????? ???? ?????? ???????? . ????????? GPIO_Speed_2MHz
2014-11-04 - ???????? ???????????? ??????? ??? CS4272
2014-11-04 - ?????? ???????? cs4272, ??????? ?????????????
2014-11-04 - ????????? ?????????? ??????? ??? process_sound
2014-11-08 - ???????? ? ????? PB12 ?? ????? PA4 ??????, ??????? ???????? ??????????. ? ?????????? ????? ??? ???????????? ??? ????, ????? ?????, ??? slave ?????????? ?????? ??? master.
2014-11-08 - SPI ???????? ?? ??????? 16 ??? (master SPI_BaudRatePrescaler_2)
2014-11-08 - ??????? ?? SPI ?????-????? ??????????/???????????
2014-11-08 - ????????? SPI ?????
2014-11-09 - ????? ?????????? CS4272 DMA
2014-11-09 - ????????? ?????????? CS4272 DMA RX
2014-11-11 - ???????? FFT ???, ?????? ???????? ???????
2014-11-11 - ???? ????? ?????????? DMA ???
2014-11-11 - ?????-????? ?????????? DMA
2014-11-12 - ?????????? ????????????? ????????????? DAC ??????
2014-11-13 - ????? ??????? ????????????? ADC / DAC ??????? ???? ???????
2014-11-14 - vertiacal scroll ??? ????????
2014-11-15 - fft ??????? ???-?? ????????
2014-11-15 - ????????? ?????, ?????? ????????? ?????? ? OnSoundDataFft
2014-11-17 - ?????????? ????????????? DAC (?? ??? ?????????????????? ???? ???????? ? DAC_InitTypeDef) - USE_FULL_ASSERT ? DEBUG
2014-11-18 - debug ??????????? ? ?????? ??????
2014-11-18 - ??????? ?? 1024 ????? ????????
2014-11-25 - ??????? +-5V
2014-12-01 - ?????????? DDS ??????????. - ????????? ???????
2014-12-06 - ?????????? ????????? ??????? ? SDR ????????? ? Raw USB ?? Virtual COM USB
2014-12-07 - ??????? I/Q ??????????????? - ???????????? Upper/Lower Side Band
2015-01-14 - ???????? ???????????? ADC_DSP.sch
2015-05-22 Migrating wiki contents from Google Code
